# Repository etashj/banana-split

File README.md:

# banana split
A split, tented keyboard with columnar staggering. Designed from scratch with ergogen, KiCad, and Fusion 360, and fully open-source. 
Runs on 18650 batteries (3.7V 1200 mAh) which provide a mass for tenting. Plan to use a clear acrylic sandwich case which. 
Design will feature clear case, white keys, brown modifiers, and yellow home "row" for a banana split. 40 keys with 4 layer cusotmizable layout. 
Uses 2 nice!nano and nice!view boards which show status. 

Making this because there arent really many ergonomic, but compact keybaord for large hand (almost oxymoronic) which also feature mechanical switches. 

More Photos/CAD model coming soon :/

### Case & Keycaps

### PCB

### ErgoPad Layout
[Design your own at this link](https://pashutk.com/ergopad/)

Features: 
 - Low profile mechanical switches
 - Low profile sculpted keycaps
 - Wireless! Uses 2 nice!nano (I think)
 - Small display for status info and idle image (2 nice!view)
 - Small/durable 3D printed case
 - Hot swappable switches
 - Reaosnably large battery
 - Easy to switch between the onboard MBP keyboard and good macOS compatibility. (this is a layout consderation). 
 - Small-ish/Portable (Ideally msaller than a handheld console like the Swithc so the case can be used)
 - Customaized for my (larger) hands
 - Fewer keycaps (less movement)

 ### Bill of Materials

| Part Name | Source | Qt | Unit Price | Price | Note |
|-----|-----|---|---|---|---|
|PCB|JLCPCB|5|3.28|16.4|min 5|
|Clear Case|JLC3DP|1|30.64|30.64||
|Keycaps|JLC3DP|40|0.3|12||
|Nice!Nano|[Typeractive](https://typeractive.xyz/products/nice-nano)|2|25|50||
|Nice!View|[Typeractive](https://typeractive.xyz/products/nice-view)|2|20|40||
|Twilight Silent Kalih Choc V1|[BeeKeeb](https://shop.beekeeb.com/product/kailh-silent-switch-linear-twilight/?srsltid=AfmBOop2ZT11Pg6cEKuNuwvuuaDNyfJdAnzfuNNDsiNcYPtR-uofrR0q)|40|1.05|42||
|Choc V1 HotSwap Sockets 100pc |[AliExpress](https://www.aliexpress.us/item/3256808288570508.html?spm=a2g0o.productlist.main.25.4ae2n4gIn4gI31&algo_pvid=5a822ad1-f8ec-4e10-a3fc-b90c5b511bf5&algo_exp_id=5a822ad1-f8ec-4e10-a3fc-b90c5b511bf5-24&pdp_ext_f=%7B%22order%22%3A%227%22%2C%22eval%22%3A%221%22%7D&pdp_npi=4%40dis%21USD%217.40%216.81%21%21%217.40%216.81%21%40210337bc17519176201104540ed05e%2112000045307138887%21sea%21US%210%21ABX&curPageLogUid=rLyCPsFTp152&utparam-url=scene%3Asearch%7Cquery_from%3A)|1|7.40|7.40|Best price is at 100 pc|
|M3 Screw and Nut Set|[AliExpress](https://www.aliexpress.us/item/3256807407760967.html?spm=a2g0o.productlist.main.50.50ddFAi9FAi94T&aem_p4p_detail=202507071242016875438172287900006501822&algo_pvid=1823b0f5-b689-4a9e-95be-df6ef2326faf&algo_exp_id=1823b0f5-b689-4a9e-95be-df6ef2326faf-47&pdp_ext_f=%7B%22order%22%3A%22147%22%2C%22eval%22%3A%221%22%7D&pdp_npi=4%40dis%21USD%213.70%212.96%21%21%213.70%212.96%21%402103244617519173212394410e940e%2112000041427988530%21sea%21US%210%21ABX&curPageLogUid=Z5tj6B7jusfV&utparam-url=scene%3Asearch%7Cquery_from%3A&search_p4p_id=202507071242016875438172287900006501822_12)|1|3.94|3.94||
|Rubber Feet 4pk|[AliExpress](https://www.aliexpress.us/item/3256809073816688.html?spm=a2g0o.detail.pcDetailTopMoreOtherSeller.1.1032JAsLJAsLcF&gps-id=pcDetailTopMoreOtherSeller&scm=1007.40050.354490.0&scm_id=1007.40050.354490.0&scm-url=1007.40050.354490.0&pvid=52a5a5e8-bf4b-41b6-8108-8eef565778c2&_t=gps-id:pcDetailTopMoreOtherSeller,scm-url:1007.40050.354490.0,pvid:52a5a5e8-bf4b-41b6-8108-8eef565778c2,tpp_buckets:668%232846%238111%231996&pdp_ext_f=%7B%22order%22%3A%221%22%2C%22eval%22%3A%221%22%2C%22sceneId%22%3A%2230050%22%7D&pdp_npi=4%40dis%21USD%210.91%210.73%21%21%210.91%210.73%21%402103244817519174567381591e3a81%2112000048590082109%21rec%21US%21%21ABX&utparam-url=scene%3ApcDetailTopMoreOtherSeller%7Cquery_from%3A)|2|0.91|1.82||
|18650 Battery Holder|[AliExpress](https://www.aliexpress.us/item/3256802855487110.html?spm=a2g0o.productlist.main.53.c05e5fcbWHw6qu&algo_pvid=3405240f-da0c-4ae4-b574-011d41f74aca&algo_exp_id=3405240f-da0c-4ae4-b574-011d41f74aca-48&pdp_ext_f=%7B%22order%22%3A%2232%22%2C%22eval%22%3A%221%22%7D&pdp_npi=4%40dis%21USD%211.16%210.66%21%21%211.16%210.66%21%402101ead817519177160806497eba65%2112000023405086083%21sea%21US%210%21ABX&curPageLogUid=vxMI0UXyYN8C&utparam-url=scene%3Asearch%7Cquery_from%3A)|2|1.16|2.32||
|18650 Cell|[LIION Wholesale](https://liionwholesale.com/products/vapcell-k25-18650-20a-35a-flat-top-2500mah-battery-genuine?variant=31330442149957)|2|3.49|6.98||
|Surface Mount Push Switch|[SparkFun](https://liionwholesale.com/products/vapcell-k25-18650-20a-35a-flat-top-2500mah-battery-genuine?variant=31330442149957)|2|1.05|2.1||

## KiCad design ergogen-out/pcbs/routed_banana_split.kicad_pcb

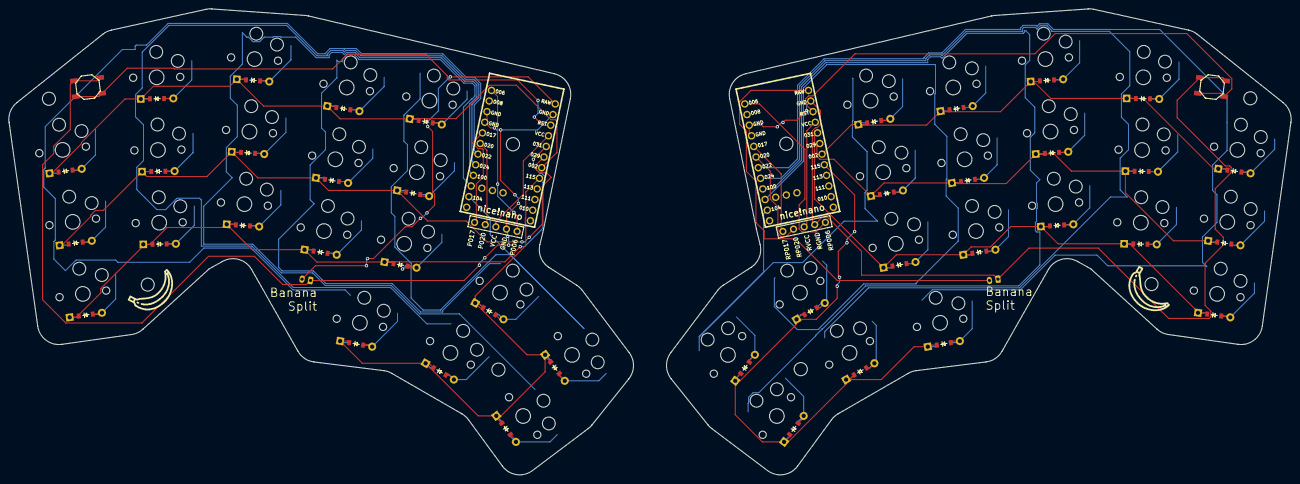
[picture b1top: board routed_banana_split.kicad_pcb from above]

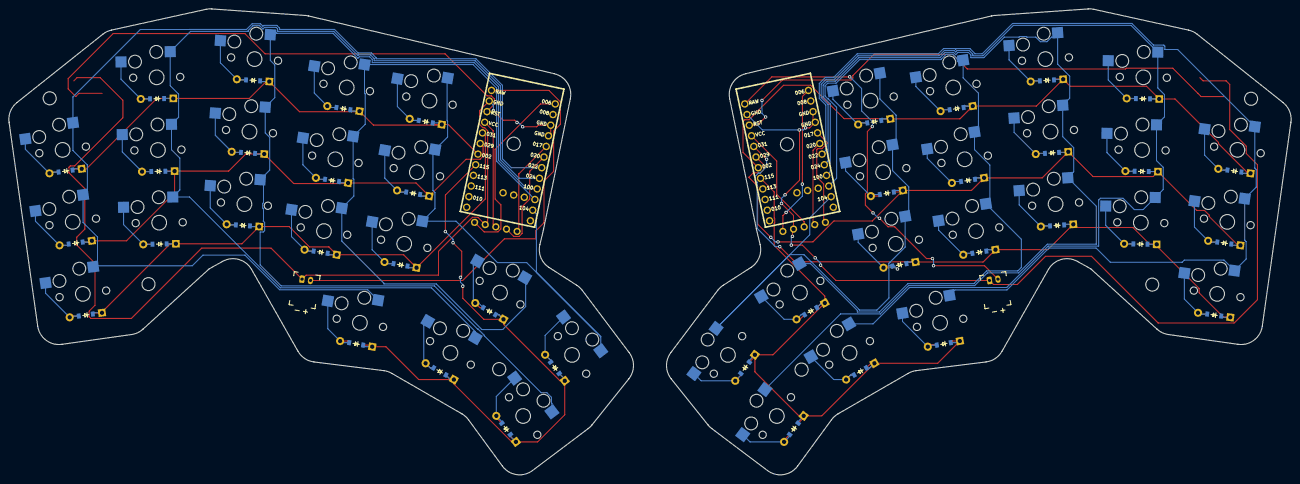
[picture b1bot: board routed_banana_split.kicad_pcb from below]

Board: 2 copper layers, 299.9 x 109.0 mm, 88 parts (2 on the bottom side), 72 nets.

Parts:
B1, B2: SW_TACT_ALPS_SKQGABE010
D1, D2, D3, D4, D5, D6, D7, D8, D9, D10, D11, D12, D13, D14, D15, D16, D17, D18, D19, D20, D21, D22, D23, D24, D25, D26, D27, D28, D29, D30, D31, D32, D33, D34, D35, D36, D37, D38, D39, D40: ComboDiode
DISP1, DISP2: display_nice_view
JST1, JST2: battery_connector_jst_ph_2
MCU1, MCU2: nice_nano
S1, S2, S3, S4, S5, S6, S7, S8, S9, S10, S11, S12, S13, S14, S15, S16, S17, S18, S19, S20, S21, S22, S23, S24, S25, S26, S27, S28, S29, S30, S31, S32, S33, S34, S35, S36, S37, S38, S39, S40: PG1350

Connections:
GND: B1.1, DISP1.4, JST1.1, MCU1.3, MCU1.4, MCU1.23
P002: D3.1, D6.1, D9.1, D12.1, D15.1, MCU1.18
P006: DISP1.5, MCU1.1
P011: MCU1.10, S10.1, S11.1, S12.1, S19.1
P017: DISP1.1, MCU1.5
P020: DISP1.2, MCU1.6
P022: MCU1.7, S1.1, S2.1, S3.1, S16.1
P024: MCU1.8, S4.1, S5.1, S6.1, S17.1
P029: D2.1, D5.1, D8.1, D11.1, D14.1, MCU1.19
P031: D1.1, D4.1, D7.1, D10.1, D13.1, MCU1.20
P100: MCU1.9, S7.1, S8.1, S9.1, S18.1
P104: MCU1.11, S13.1, S14.1, S15.1, S20.1
P115: D16.1, D17.1, D18.1, D19.1, D20.1, MCU1.17
RAW: JST1.2, MCU1.24
RGND: B2.1, DISP2.4, JST2.1, MCU2.3, MCU2.4, MCU2.23
RP002: D23.1, D26.1, D29.1, D32.1, D35.1, MCU2.18
RP006: DISP2.5, MCU2.1
RP011: MCU2.10, S30.1, S31.1, S32.1, S39.1
RP017: DISP2.1, MCU2.5
RP020: DISP2.2, MCU2.6
RP022: MCU2.7, S21.1, S22.1, S23.1, S36.1
RP024: MCU2.8, S24.1, S25.1, S26.1, S37.1
RP029: D22.1, D25.1, D28.1, D31.1, D34.1, MCU2.19
RP031: D21.1, D24.1, D27.1, D30.1, D33.1, MCU2.20
RP100: MCU2.9, S27.1, S28.1, S29.1, S38.1
RP104: MCU2.11, S33.1, S34.1, S35.1, S40.1
RP115: D36.1, D37.1, D38.1, D39.1, D40.1, MCU2.17
RRAW: JST2.2, MCU2.24
RRST: B2.2, MCU2.22
RST: B1.2, MCU1.22
RVCC: DISP2.3, MCU2.21
VCC: DISP1.3, MCU1.21
home_thumb: D17.2, S17.2
in_default: D19.2, S19.2
in_thumb: D16.2, S16.2
index_bottom: D10.2, S10.2
index_home: D11.2, S11.2
index_top: D12.2, S12.2
indexfar_bottom: D13.2, S13.2
indexfar_home: D14.2, S14.2
indexfar_top: D15.2, S15.2
middle_bottom: D7.2, S7.2
middle_home: D8.2, S8.2
middle_top: D9.2, S9.2
mirror_home_thumb: D37.2, S37.2
mirror_in_default: D39.2, S39.2
mirror_in_thumb: D36.2, S36.2
mirror_index_bottom: D30.2, S30.2
mirror_index_home: D31.2, S31.2
mirror_index_top: D32.2, S32.2
mirror_indexfar_bottom: D33.2, S33.2
mirror_indexfar_home: D34.2, S34.2
mirror_indexfar_top: D35.2, S35.2
mirror_middle_bottom: D27.2, S27.2
mirror_middle_home: D28.2, S28.2
mirror_middle_top: D29.2, S29.2
mirror_out_default: D40.2, S40.2
mirror_out_thumb: D38.2, S38.2
mirror_pinky_bottom: D21.2, S21.2
mirror_pinky_home: D22.2, S22.2
mirror_pinky_top: D23.2, S23.2
mirror_ring_bottom: D24.2, S24.2
mirror_ring_home: D25.2, S25.2
mirror_ring_top: D26.2, S26.2
out_default: D20.2, S20.2
out_thumb: D18.2, S18.2
pinky_bottom: D1.2, S1.2
pinky_home: D2.2, S2.2
pinky_top: D3.2, S3.2
ring_bottom: D4.2, S4.2
ring_home: D5.2, S5.2
ring_top: D6.2, S6.2

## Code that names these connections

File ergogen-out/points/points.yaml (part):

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        autobind: 10
        skip: false
        asym: both
        colrow: pinky_bottom
        name: leftmain_pinky_bottom
        zone:
            columns:
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        autobind: 10
        skip: false
        asym: both
        colrow: pinky_home
        name: leftmain_pinky_home
        zone:
            columns:
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        autobind: 10
        skip: false
        asym: both
        colrow: pinky_top
        name: leftmain_pinky_top
        zone:
            columns:
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        autobind: 10
        skip: false
        asym: both
        colrow: mirror_pinky_bottom
        name: mirror_leftmain_pinky_bottom
        zone:
            columns:
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        autobind: 10
        skip: false
        asym: both
        colrow: mirror_pinky_home
        name: mirror_leftmain_pinky_home
        zone:
            columns:
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        autobind: 10
        skip: false
        asym: both
        colrow: mirror_pinky_top
        name: mirror_leftmain_pinky_top
        zone:
            columns:
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
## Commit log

2025-07-04 ergopad + inital commit
2025-07-05 first ergogen
2025-07-05 layout plan
2025-07-05 choc spacing:
2025-07-06 boards complete
2025-07-06 renamed
2025-07-06 main pcb layout
2025-07-06 net names for left
2025-07-06 fix net names
2025-07-06 remove reversibility
2025-07-07 pcb routed
2025-07-07 creat BOM.xlsx
2025-07-07 render 1
2025-07-07 Added case
2025-07-07 finishing up
2025-07-07 cad files
2025-07-07 update render
